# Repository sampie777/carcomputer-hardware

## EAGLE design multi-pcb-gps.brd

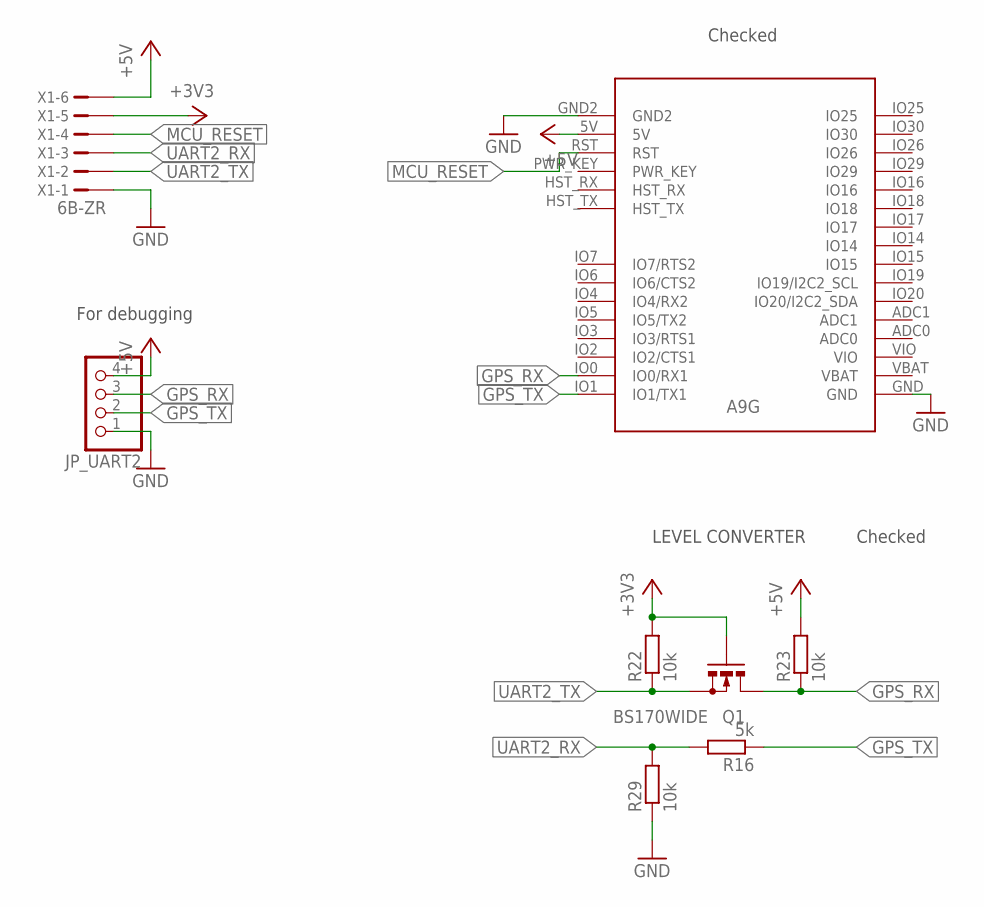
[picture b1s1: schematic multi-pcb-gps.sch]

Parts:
JP_UART2: PINHD-1X4; 1X04
Q1: BS170WIDE; SOT54E2
R16: 5k; 0207/7
R22, R23, R29: 10k; 0207/7
U$6: A9G
X1: 6B-ZR; B6B-ZR2.5

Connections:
+3V3: Q1.G, R22.2, X1.5
+5V: JP_UART2.4, R23.2, U$6.5V, X1.6
GND: JP_UART2.1, R29.1, U$6.GND, U$6.GND2, X1.1
GPS_RX: JP_UART2.3, Q1.D, R23.1, U$6.IO0 (IO0/RX1)
GPS_TX: JP_UART2.2, R16.1, U$6.IO1 (IO1/TX1)
MCU_RESET: U$6.RST, X1.4
UART2_RX: R16.2, R29.2, X1.3
UART2_TX: Q1.S, R22.1, X1.2

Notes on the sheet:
Checked
LEVEL CONVERTER
For debugging

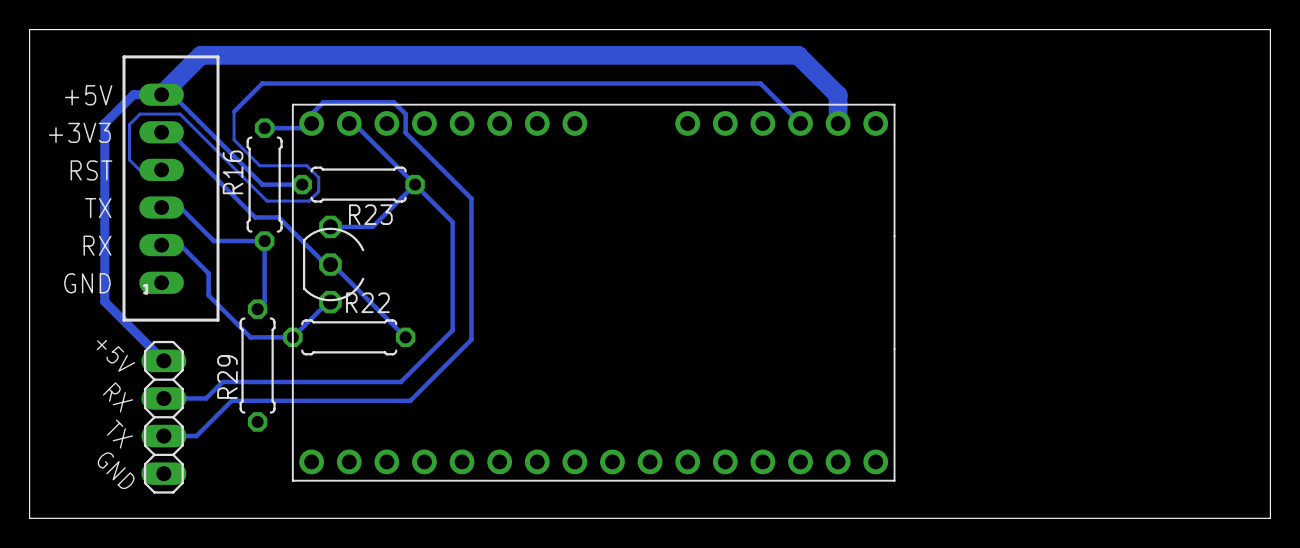
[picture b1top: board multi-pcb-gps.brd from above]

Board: 2 copper layers, 83.8 x 33.0 mm, 8 parts (0 on the bottom side), 8 nets.

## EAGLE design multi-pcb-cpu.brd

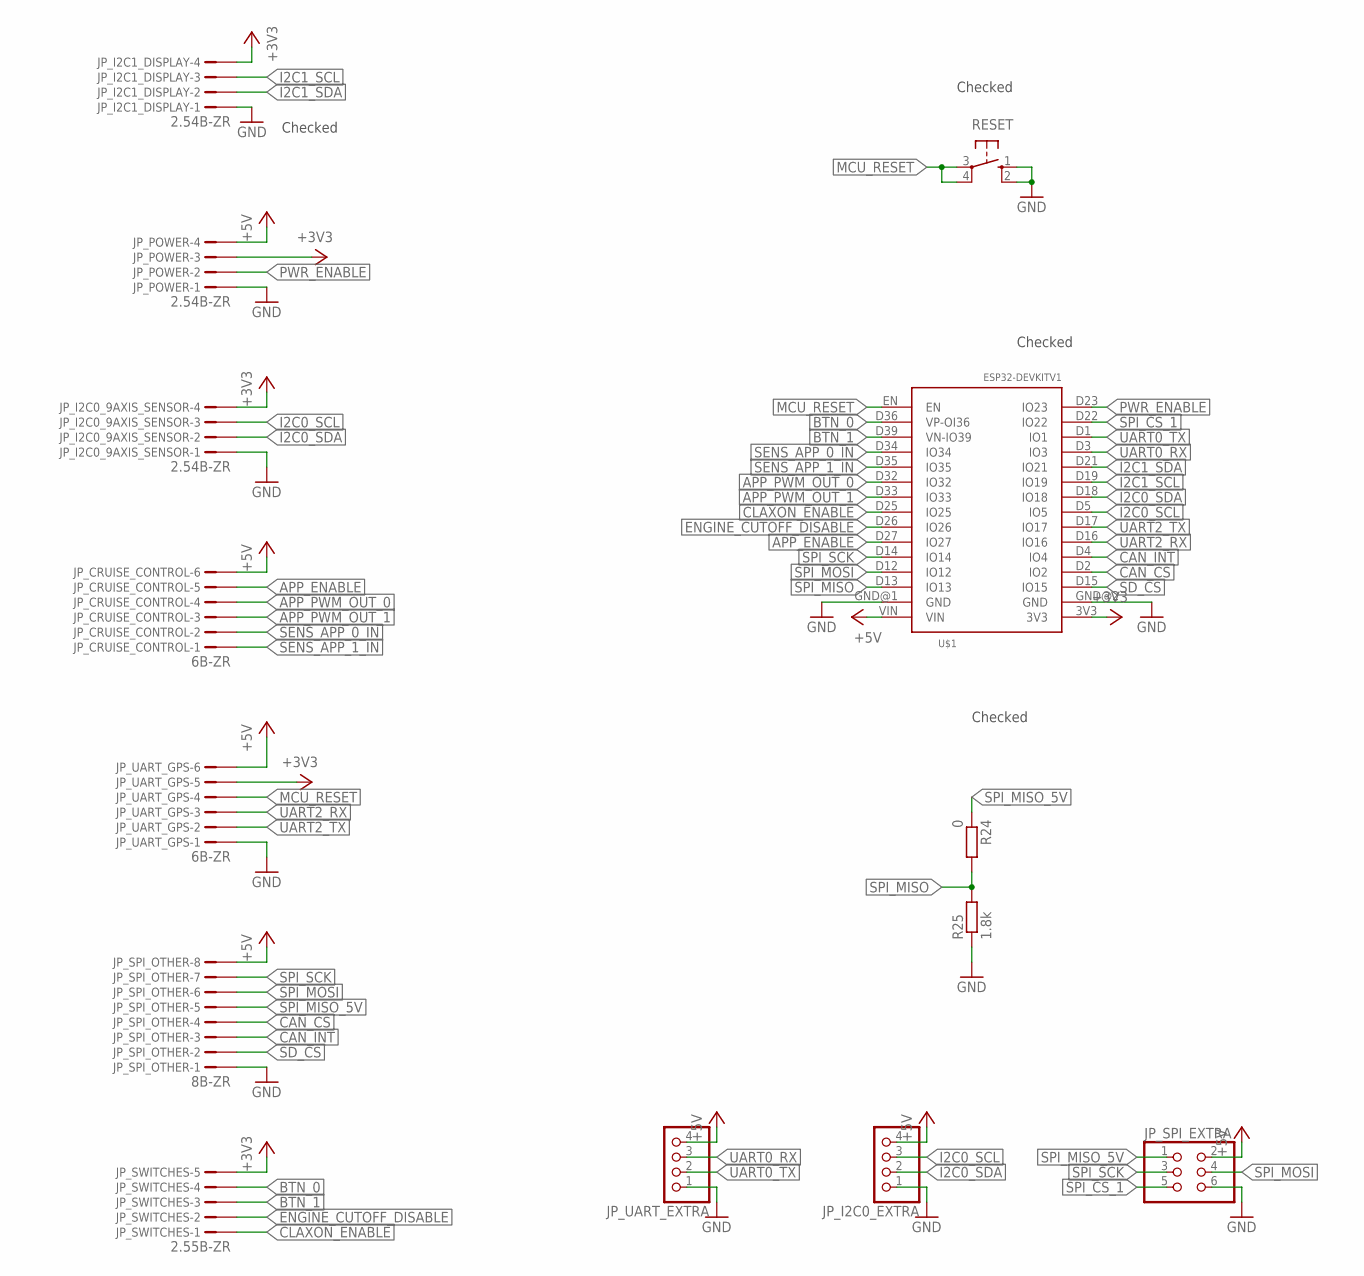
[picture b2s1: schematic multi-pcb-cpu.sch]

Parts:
JP_CRUISE_CONTROL: 6B-ZR; B6B-ZR2.5
JP_I2C0_9AXIS_SENSOR, JP_I2C1_DISPLAY: 2.54B-ZR; B4B-ZR2.5
JP_I2C0_EXTRA: PINHD-1X4; 1X04
JP_POWER: 2.54B-ZR; B4B-ZR2.5
JP_SPI_EXTRA: PINHD-2X3; 2X03
JP_SPI_OTHER: 8B-ZR; B8B-ZR2.5
JP_SWITCHES: 2.55B-ZR; B5B-ZR2.5
JP_UART_EXTRA: PINHD-1X4; 1X04
JP_UART_GPS: 6B-ZR; B6B-ZR2.5
R24: 0; 0207/7
R25: 1.8k; 0207/7
RESET: 10-XX; B3F-10XX
U$1: ESP32DEVKITV1; ESP32-DEVKITV1

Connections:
+3V3: JP_I2C0_9AXIS_SENSOR.4, JP_I2C1_DISPLAY.4, JP_POWER.3, JP_SWITCHES.5, JP_UART_GPS.5, U$1.3V3
+5V: JP_CRUISE_CONTROL.6, JP_I2C0_EXTRA.4, JP_POWER.4, JP_SPI_EXTRA.2, JP_SPI_OTHER.8, JP_UART_EXTRA.4, JP_UART_GPS.6, U$1.VIN
APP_ENABLE: JP_CRUISE_CONTROL.5, U$1.D27 (IO27)
APP_PWM_OUT_0: JP_CRUISE_CONTROL.4, U$1.D32 (IO32)
APP_PWM_OUT_1: JP_CRUISE_CONTROL.3, U$1.D33 (IO33)
BTN_0: JP_SWITCHES.4, U$1.D36 (VP-OI36)
BTN_1: JP_SWITCHES.3, U$1.D39 (VN-IO39)
CAN_CS: JP_SPI_OTHER.4, U$1.D2 (IO2)
CAN_INT: JP_SPI_OTHER.3, U$1.D4 (IO4)
CLAXON_ENABLE: JP_SWITCHES.1, U$1.D25 (IO25)
ENGINE_CUTOFF_DISABLE: JP_SWITCHES.2, U$1.D26 (IO26)
GND: JP_I2C0_9AXIS_SENSOR.1, JP_I2C0_EXTRA.1, JP_I2C1_DISPLAY.1, JP_POWER.1, JP_SPI_EXTRA.6, JP_SPI_OTHER.1, JP_UART_EXTRA.1, JP_UART_GPS.1, R25.1, RESET.1 (S), RESET.2 (S1), U$1.GND@1 (GND), U$1.GND@2 (GND)
I2C0_SCL: JP_I2C0_9AXIS_SENSOR.3, JP_I2C0_EXTRA.3, U$1.D5 (IO5)
I2C0_SDA: JP_I2C0_9AXIS_SENSOR.2, JP_I2C0_EXTRA.2, U$1.D18 (IO18)
I2C1_SCL: JP_I2C1_DISPLAY.3, U$1.D19 (IO19)
I2C1_SDA: JP_I2C1_DISPLAY.2, U$1.D21 (IO21)
MCU_RESET: JP_UART_GPS.4, RESET.3, RESET.4 (P1), U$1.EN
PWR_ENABLE: JP_POWER.2, U$1.D23 (IO23)
SD_CS: JP_SPI_OTHER.2, U$1.D15 (IO15)
SENS_APP_0_IN: JP_CRUISE_CONTROL.2, U$1.D34 (IO34)
SENS_APP_1_IN: JP_CRUISE_CONTROL.1, U$1.D35 (IO35)
SPI_CS_1: JP_SPI_EXTRA.5, U$1.D22 (IO22)
SPI_MISO: R24.2, R25.2, U$1.D13 (IO13)
SPI_MISO_5V: JP_SPI_EXTRA.1, JP_SPI_OTHER.5, R24.1
SPI_MOSI: JP_SPI_EXTRA.4, JP_SPI_OTHER.6, U$1.D12 (IO12)
SPI_SCK: JP_SPI_EXTRA.3, JP_SPI_OTHER.7, U$1.D14 (IO14)
UART0_RX: JP_UART_EXTRA.3, U$1.D3 (IO3)
UART0_TX: JP_UART_EXTRA.2, U$1.D1 (IO1)
UART2_RX: JP_UART_GPS.3, U$1.D16 (IO16)
UART2_TX: JP_UART_GPS.2, U$1.D17 (IO17)

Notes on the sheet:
Checked

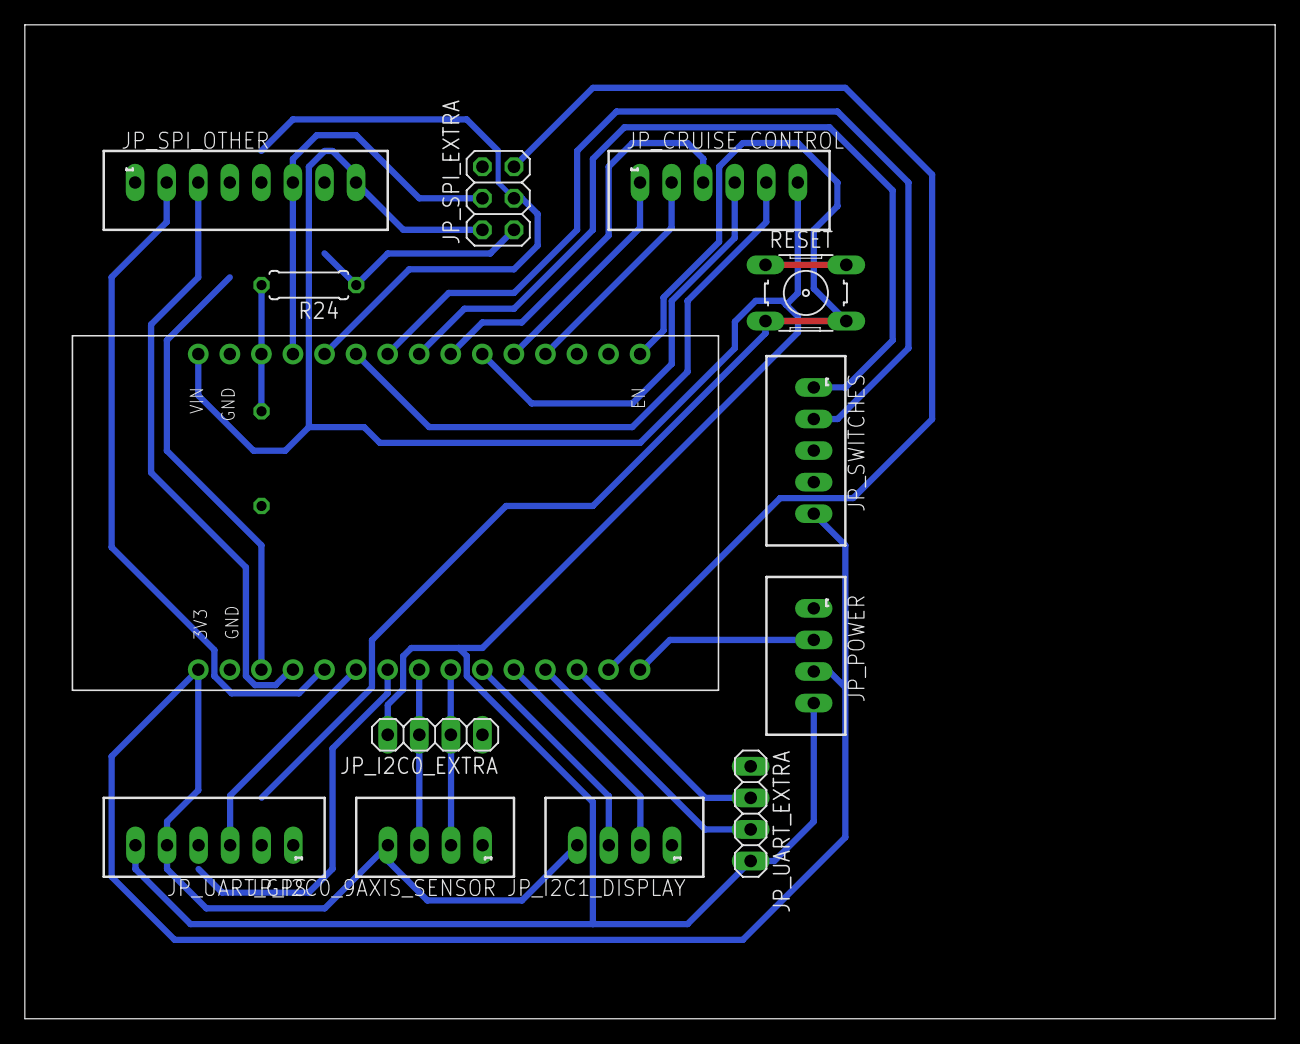
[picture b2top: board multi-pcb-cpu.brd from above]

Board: 2 copper layers, 100.6 x 80.0 mm, 14 parts (1 on the bottom side), 30 nets.

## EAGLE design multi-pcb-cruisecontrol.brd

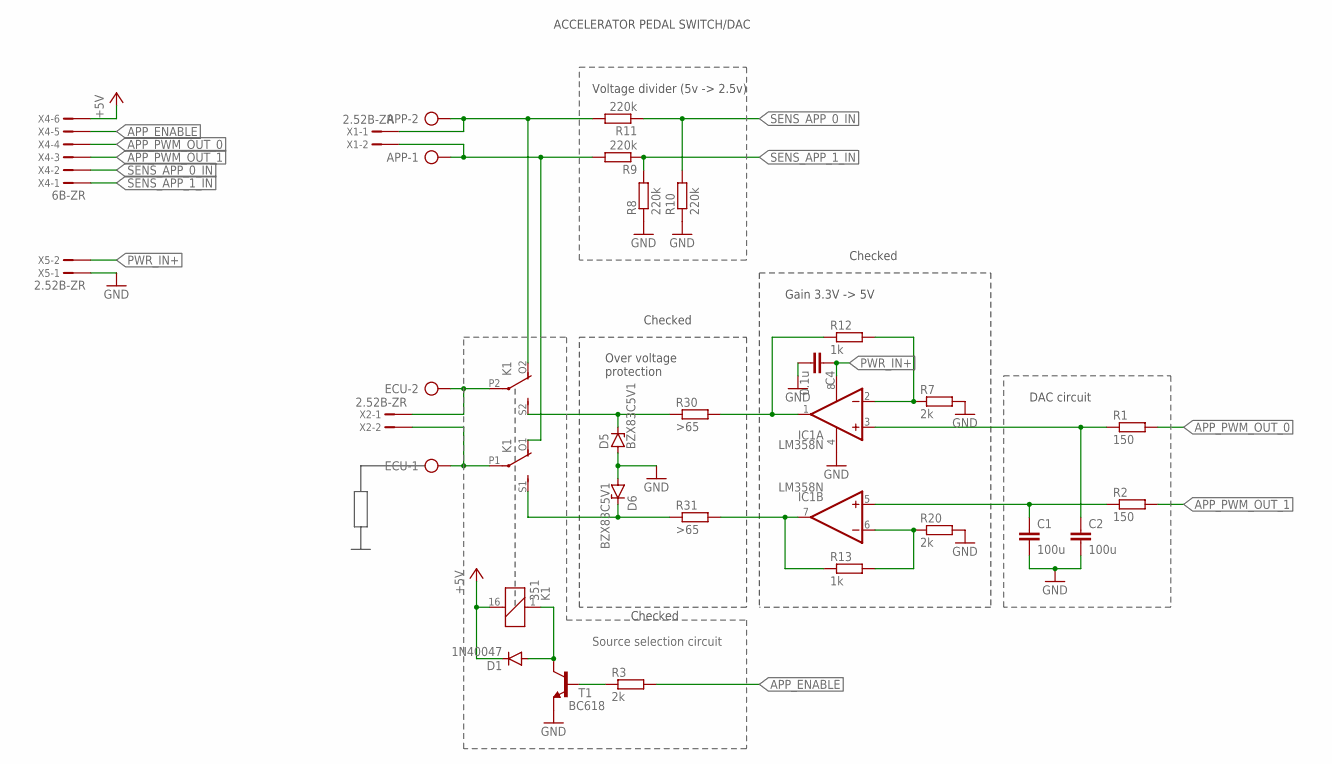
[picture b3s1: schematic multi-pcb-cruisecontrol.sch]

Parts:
APP: AK300/2
C1, C2: 100u; C025-050X050
C4: 0.1u; C025-050X050
D1: 1N40047; DO41-7.6
D5, D6: BZX83C5V1; DO41Z7.6
ECU: AK300/2
IC1: LM358N; DIL08
K1: 351
R1, R2: 150; 0207/7
R3, R7, R20: 2k; 0207/7
R8, R9, R10, R11: 220k; 0207/7
R12, R13: 1k; 0207/7
R30, R31: >65; 0207/7
T1: BC618; TO92-EBC
X1, X2, X5: 2.52B-ZR; B2B-ZR2.5
X4: 6B-ZR; B6B-ZR2.5

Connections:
+5V: D1.C, K1.16 (2), X4.6
APP_0_IN: APP.2, K1.O2 (O), R11.2, X1.1
APP_1_IN: APP.1, K1.O1 (O), R9.2, X1.2
APP_ENABLE: R3.2, X4.5
APP_PWM_OUT_0: R1.2, X4.4
APP_PWM_OUT_1: R2.2, X4.3
GND: C1.2, C2.2, C4.2, D5.A, D6.A, IC1.4 (V-), R7.2, R8.1, R10.1, R20.2, T1.E, X5.1
unnamed: D1.A, K1.1, T1.C
unnamed: R3.1, T1.B
unnamed: D6.C, K1.S1 (S), R31.1
unnamed: IC1.1 (OUT), R12.1, R30.2
unnamed: ECU.2, K1.P2, X2.1
unnamed: ECU.1, K1.P1, X2.2
unnamed: C2.1, IC1.3 (+IN), R1.1
unnamed: C1.1, IC1.5 (+IN), R2.1
unnamed: IC1.2 (-IN), R7.1, R12.2
unnamed: IC1.6 (-IN), R13.2, R20.1
unnamed: D5.C, K1.S2 (S), R30.1
unnamed: IC1.7 (OUT), R13.1, R31.2
PWR_IN+: C4.1, IC1.8 (V+), X5.2
SENS_APP_0_IN: R10.2, R11.1, X4.2
SENS_APP_1_IN: R8.2, R9.1, X4.1

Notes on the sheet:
Voltage divider (5v -> 2.5v)
DAC circuit
Source selection circuit
ACCELERATOR PEDAL SWITCH/DAC
Gain 3.3V -> 5V
Over voltage protection
Checked

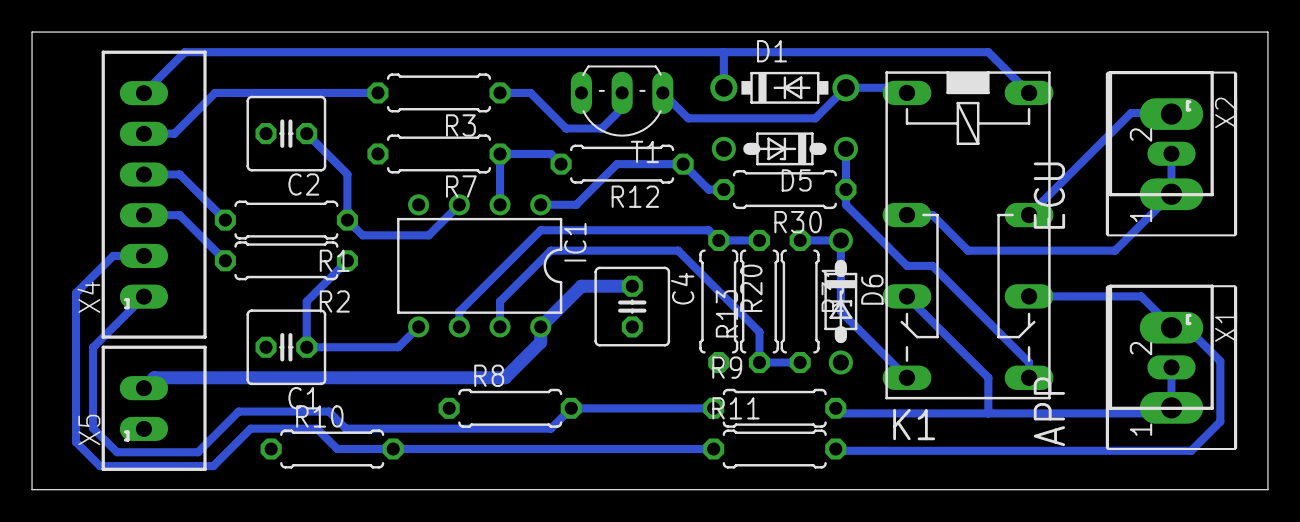
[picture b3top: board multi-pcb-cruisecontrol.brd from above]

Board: 2 copper layers, 77.1 x 28.6 mm, 28 parts (0 on the bottom side), 22 nets.

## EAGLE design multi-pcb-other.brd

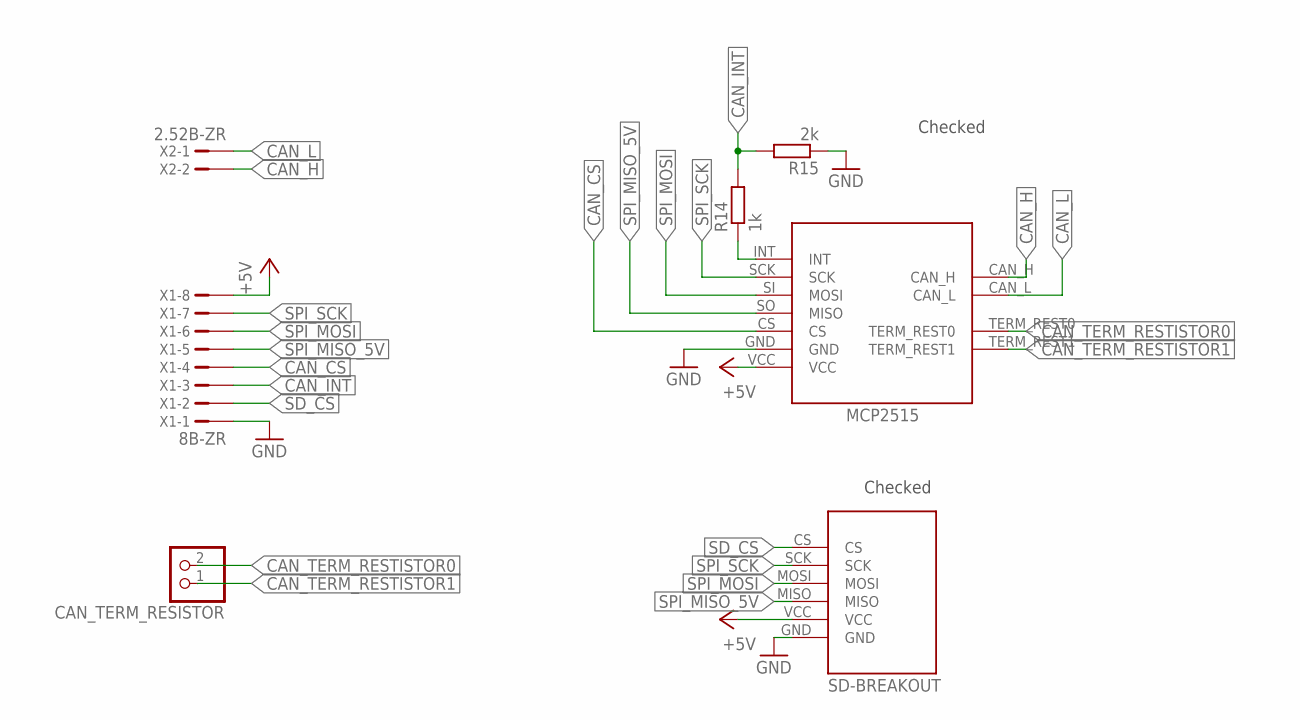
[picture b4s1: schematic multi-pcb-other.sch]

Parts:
CAN_TERM_RESISTOR: PINHD-1X2; 1X02
R14: 1k; 0207/10
R15: 2k; 0207/10
U$2: MCP2515_DEVBOARDMCP2515_DEVBOARD_INVERTED_NODRILL; MCP2515_DEVBOARD_INVERTED_NODRILL
U$5: HKD-MICRO-SD-BREAKOUT; HKD-MICRO-SD-BREAKOUT_NODRILL
X1: 8B-ZR; B8B-ZR2.5
X2: 2.52B-ZR; B2B-ZR2.5

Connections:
+5V: U$2.VCC, U$5.VCC, X1.8
CAN_CS: U$2.CS, X1.4
CAN_H: U$2.CAN_H, X2.2
CAN_INT: R14.2, R15.2, X1.3
CAN_L: U$2.CAN_L, X2.1
CAN_TERM_RESTISTOR0: CAN_TERM_RESISTOR.2, U$2.TERM_REST0
CAN_TERM_RESTISTOR1: CAN_TERM_RESISTOR.1, U$2.TERM_REST1
GND: R15.1, U$2.GND, U$5.GND, X1.1
unnamed: R14.1, U$2.INT
SD_CS: U$5.CS, X1.2
SPI_MISO_5V: U$2.SO (MISO), U$5.MISO, X1.5
SPI_MOSI: U$2.SI (MOSI), U$5.MOSI, X1.6
SPI_SCK: U$2.SCK, U$5.SCK, X1.7

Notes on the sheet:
Checked

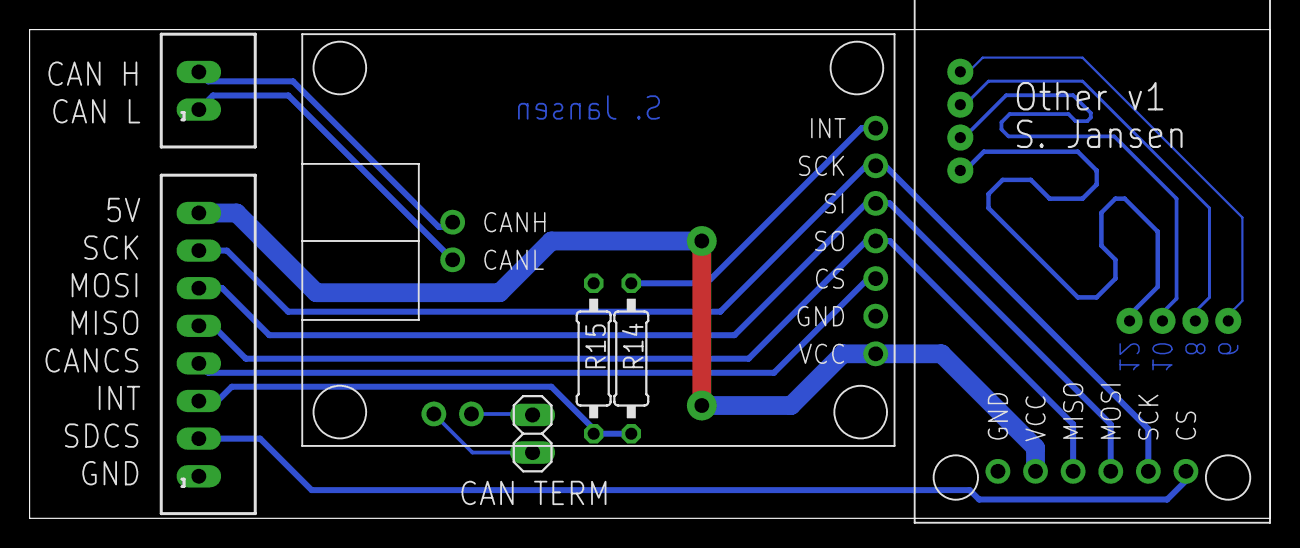
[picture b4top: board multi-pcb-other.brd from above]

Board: 2 copper layers, 83.8 x 33.0 mm, 7 parts (0 on the bottom side), 13 nets.

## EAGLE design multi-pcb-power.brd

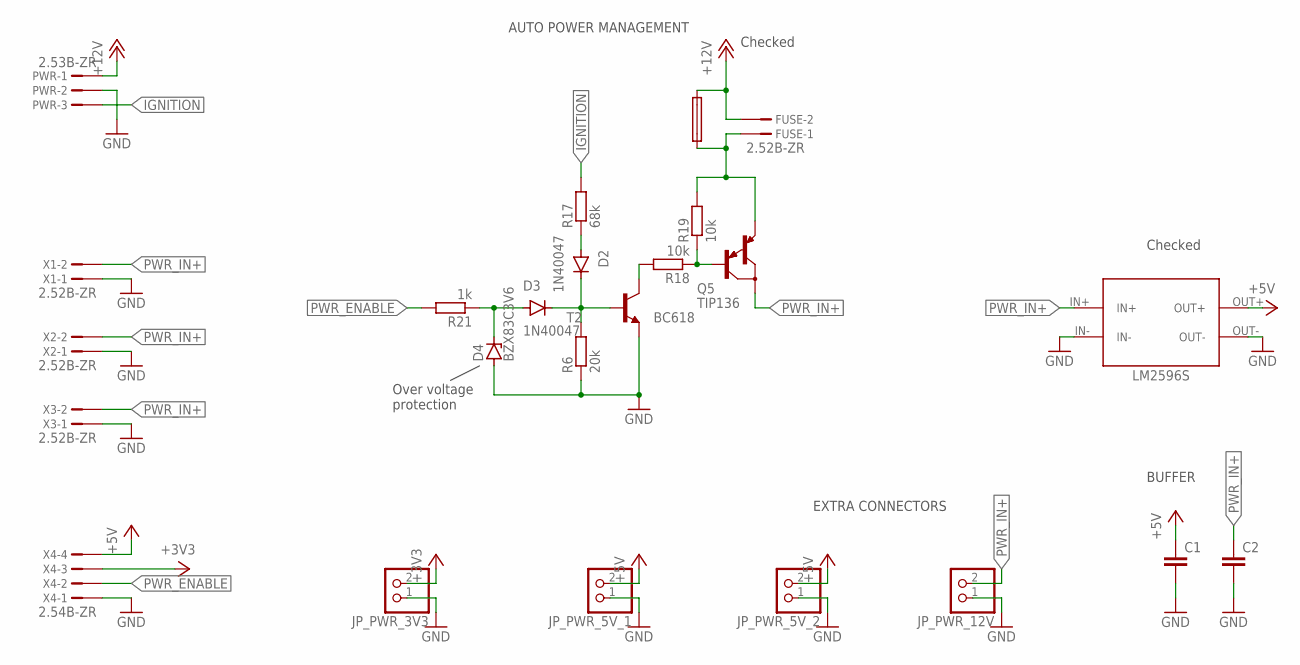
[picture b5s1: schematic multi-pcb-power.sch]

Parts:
C1, C2: C-EU050-075X075; C050-075X075
D2, D3: 1N40047; DO41-7.6
D4: BZX83C3V6; DO41Z7.6
FUSE: 2.52B-ZR; B2B-ZR2.5
JP_PWR_3V3, JP_PWR_5V_1, JP_PWR_5V_2, JP_PWR_12V: PINHD-1X2; 1X02
PWR: 2.53B-ZR; B3B-ZR2.5
Q5: TIP136; TO220
R6: 20k; 0207/7
R17: 68k; 0207/7
R18, R19: 10k; 0207/7
R21: 1k; 0207/7
T2: BC618; TO92-EBC
U$1: FUSE; FB-5X20
U$4: LM2596S
X1, X2, X3: 2.52B-ZR; B2B-ZR2.5
X4: 2.54B-ZR; B4B-ZR2.5

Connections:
+3V3: JP_PWR_3V3.2, X4.3
+5V: C1.1, JP_PWR_5V_1.2, JP_PWR_5V_2.2, U$4.OUT+, X4.4
+12V: FUSE.2, PWR.1, U$1.P$3, U$1.P$4
GND: C1.2, C2.2, D4.A, JP_PWR_3V3.1, JP_PWR_5V_1.1, JP_PWR_5V_2.1, JP_PWR_12V.1, PWR.2, R6.1, T2.E, U$4.IN-, U$4.OUT-, X1.1, X2.1, X3.1, X4.1
IGNITION: PWR.3, R17.2
unnamed: D2.C, D3.C, R6.2, T2.B
unnamed: D3.A, D4.C, R21.1
unnamed: D2.A, R17.1
unnamed: Q5.1 (B), R18.1, R19.1
unnamed: R18.2, T2.C
unnamed: FUSE.1, Q5.3 (E), R19.2, U$1.P$1, U$1.P$2
PWR_ENABLE: R21.2, X4.2
PWR_IN+: C2.1, JP_PWR_12V.2, Q5.2 (C), U$4.IN+, X1.2, X2.2, X3.2

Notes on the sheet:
Over voltage protection
AUTO POWER MANAGEMENT
EXTRA CONNECTORS
Checked
BUFFER

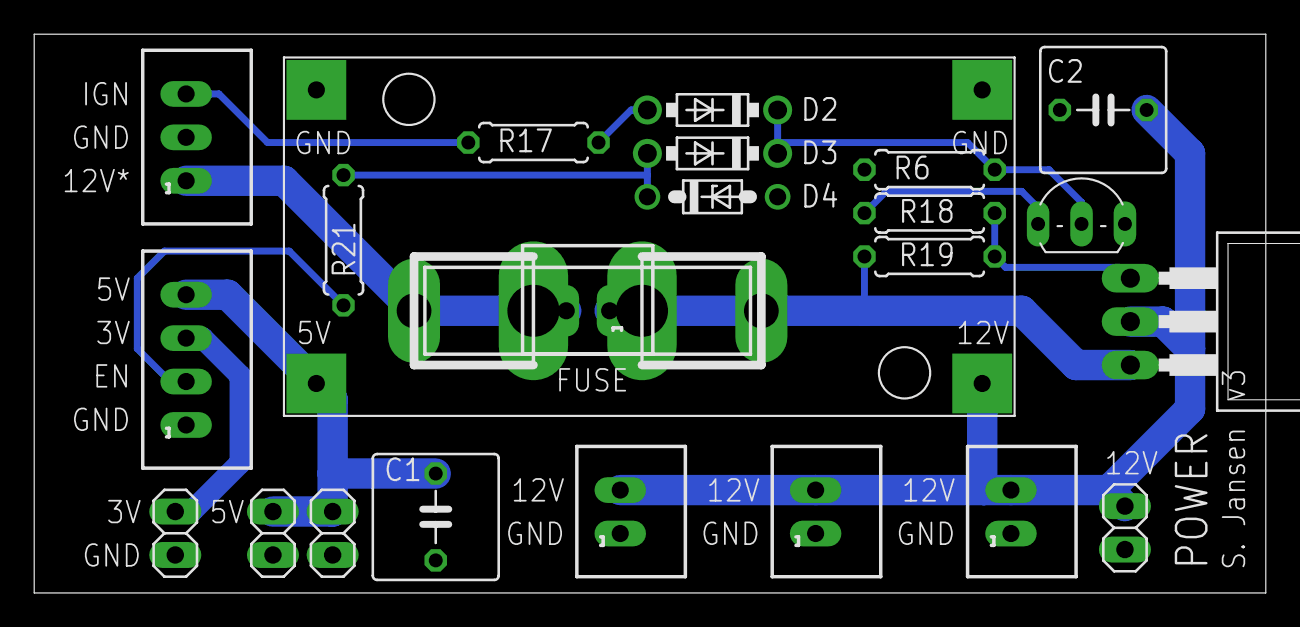
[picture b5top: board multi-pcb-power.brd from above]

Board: 2 copper layers, 72.1 x 32.7 mm, 24 parts (0 on the bottom side), 13 nets.

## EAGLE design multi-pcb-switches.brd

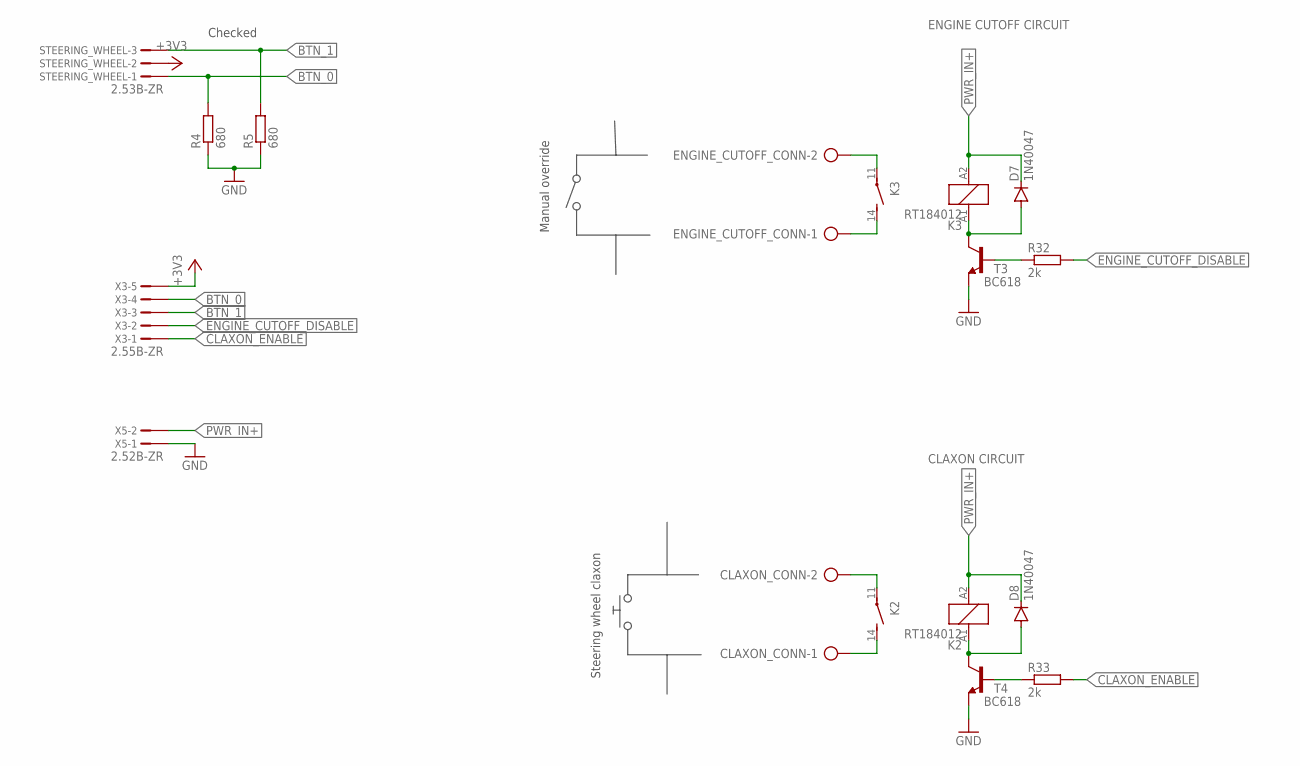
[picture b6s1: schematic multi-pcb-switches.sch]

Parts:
CLAXON_CONN: AK300/2
D7, D8: 1N40047; DO41-7.6
ENGINE_CUTOFF_CONN: AK300/2
K2, K3: RT184012; RT-N/O12A3.5
R4, R5: 680; 0207/7
R32, R33: 2k; 0207/7
STEERING_WHEEL: 2.53B-ZR; B3B-ZR2.5
T3, T4: BC618; TO92-EBC
X3: 2.55B-ZR; B5B-ZR2.5
X5: 2.52B-ZR; B2B-ZR2.5

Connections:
+3V3: STEERING_WHEEL.2, X3.5
BTN_0: R4.2, STEERING_WHEEL.1, X3.4
BTN_1: R5.2, STEERING_WHEEL.3, X3.3
CLAXON_ENABLE: R33.2, X3.1
ENGINE_CUTOFF_DISABLE: R32.2, X3.2
GND: R4.1, R5.1, T3.E, T4.E, X5.1
unnamed: ENGINE_CUTOFF_CONN.2, K3.11
unnamed: ENGINE_CUTOFF_CONN.1, K3.14 (S)
unnamed: D7.A, K3.A1 (1), T3.C
unnamed: D8.A, K2.A1 (1), T4.C
unnamed: R33.1, T4.B
unnamed: R32.1, T3.B
unnamed: CLAXON_CONN.2, K2.11
unnamed: CLAXON_CONN.1, K2.14 (S)
PWR_IN+: D7.C, D8.C, K2.A2 (2), K3.A2 (2), X5.2

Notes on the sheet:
Checked
ENGINE CUTOFF CIRCUIT
Manual override
CLAXON CIRCUIT
Steering wheel claxon

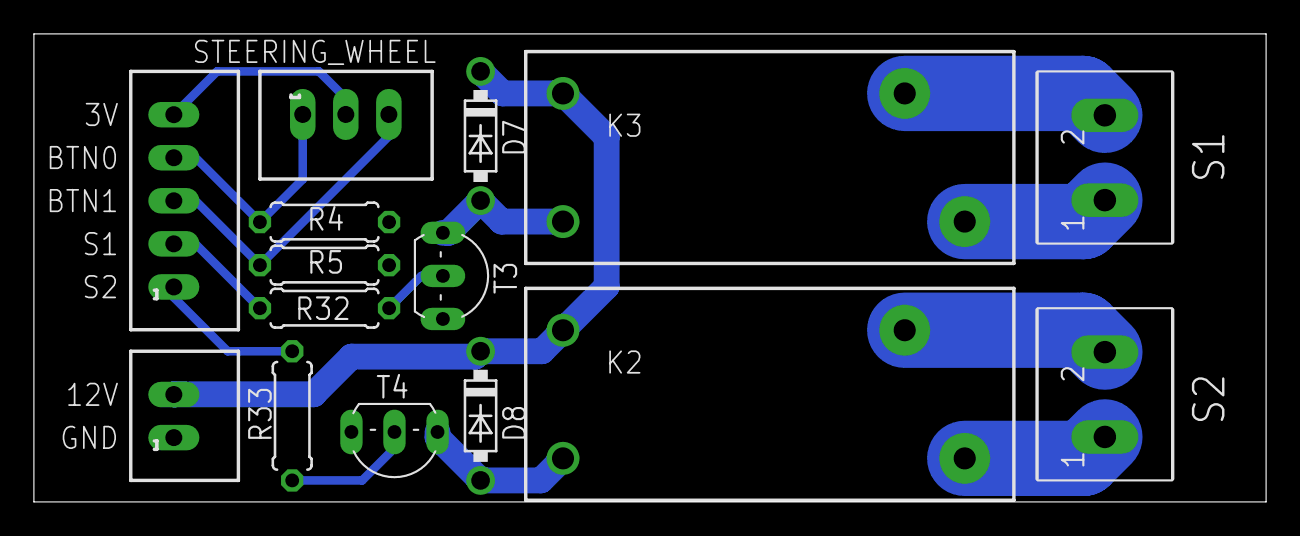
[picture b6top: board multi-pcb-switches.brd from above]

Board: 2 copper layers, 72.7 x 27.6 mm, 15 parts (0 on the bottom side), 15 nets.

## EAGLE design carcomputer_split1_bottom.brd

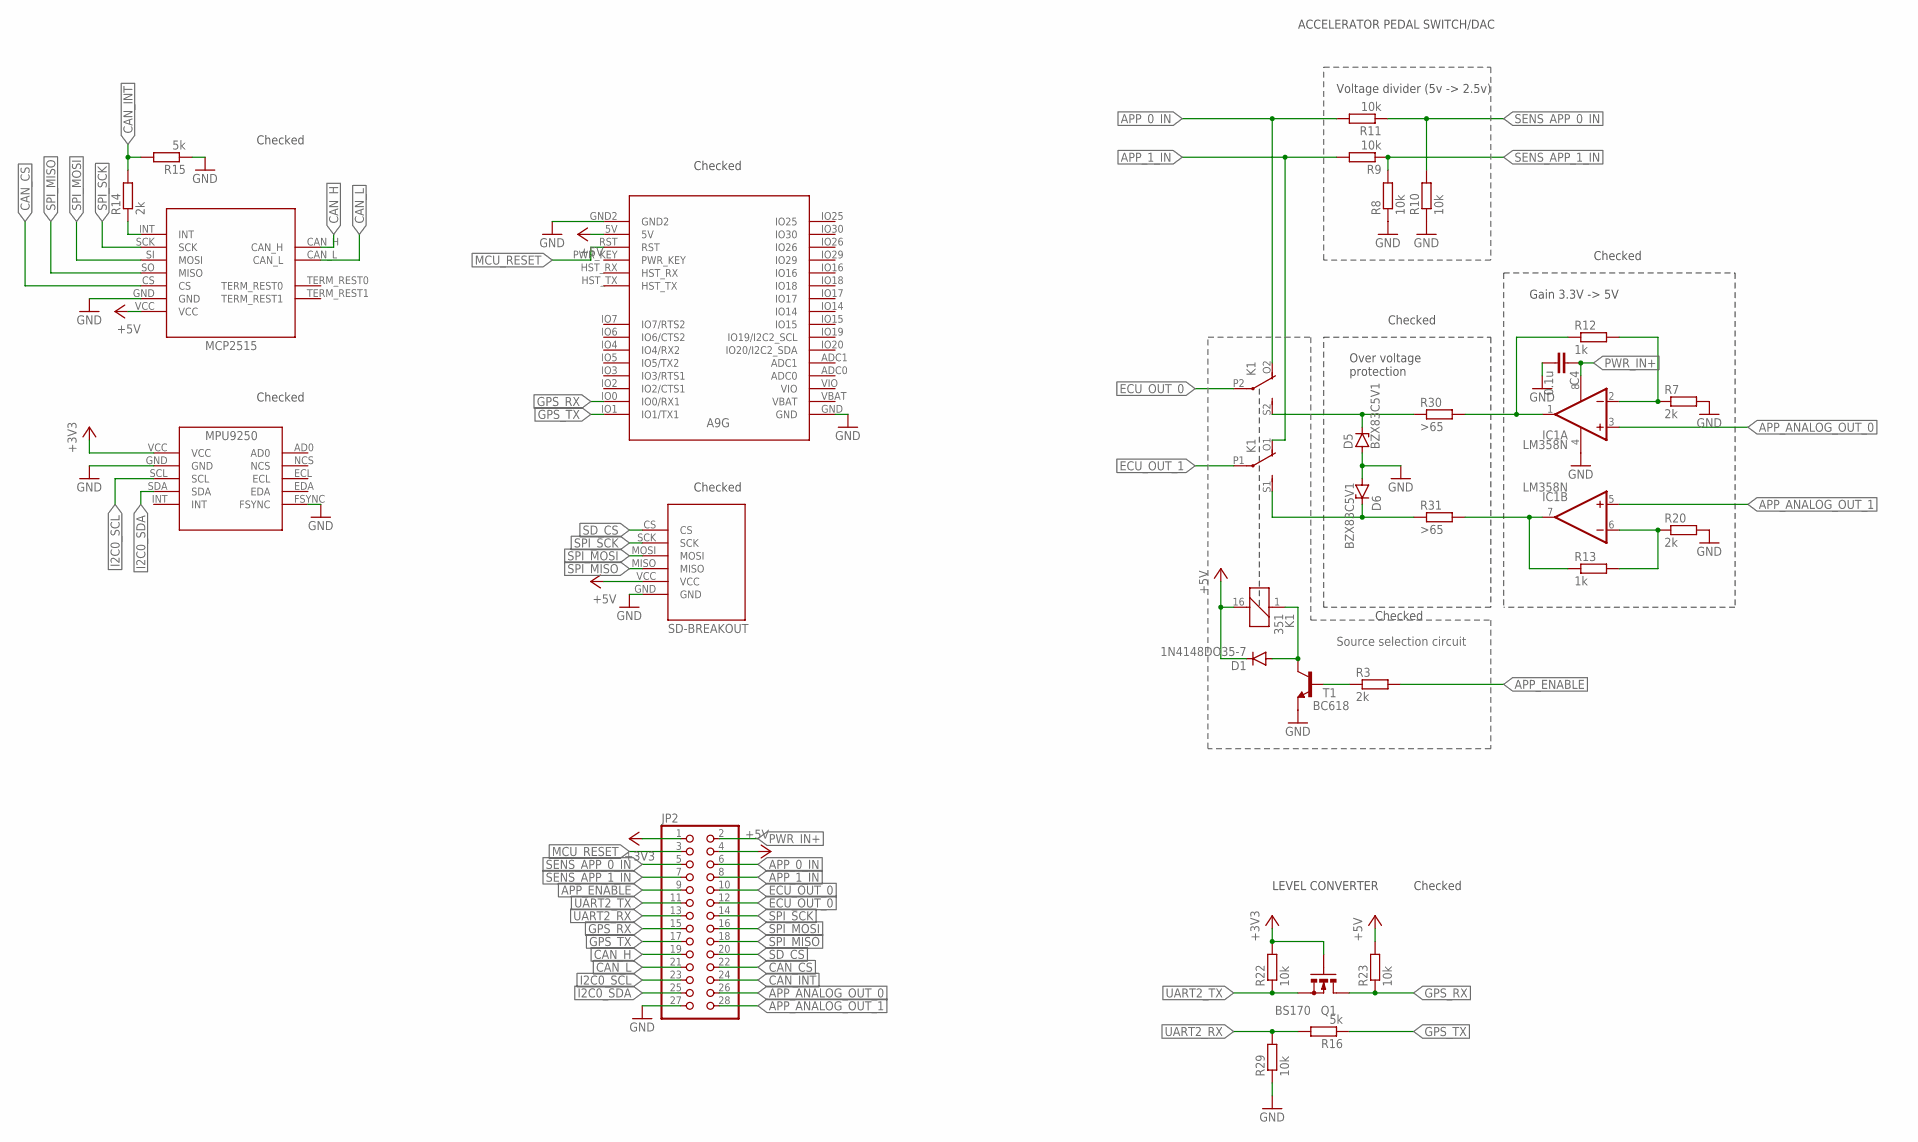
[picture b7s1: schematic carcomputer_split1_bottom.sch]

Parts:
C4: 0.1u; C025-050X050
D1: 1N4148DO35-7; DO35-7
D5, D6: BZX83C5V1; DO41Z10
IC1: LM358N; DIL08
JP2: PINHD-2X14; 2X14
K1: 351
Q1: BS170; SOT54E
R3, R7, R14, R20: 2k; 0207/7
R8, R9, R10, R11, R22, R23, R29: 10k; 0207/7
R12, R13: 1k; 0207/7
R15, R16: 5k; 0207/7
R30, R31: >65; 0207/7
T1: BC618; TO92-EBC
U$2: MCP2515_DEVBOARDINVERTED; MCP2515_DEVBOARD_INVERTED
U$3: MPU9250_BREAKOUT
U$5: HKD-MICRO-SD-BREAKOUT
U$6: A9G

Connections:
+3V3: JP2.1, Q1.G, R22.2, U$3.VCC
+5V: D1.C, JP2.4, K1.16 (2), R23.2, U$2.VCC, U$5.VCC, U$6.5V
APP_0_IN: JP2.6, K1.O2 (O), R11.2
APP_1_IN: JP2.8, K1.O1 (O), R9.2
APP_ANALOG_OUT_0: IC1.3 (+IN), JP2.26
APP_ANALOG_OUT_1: IC1.5 (+IN), JP2.28
APP_ENABLE: JP2.9, R3.2
CAN_CS: JP2.22, U$2.CS
CAN_H: JP2.19, U$2.CAN_H
CAN_INT: JP2.24, R14.2, R15.2
CAN_L: JP2.21, U$2.CAN_L
ECU_OUT_0: JP2.10, JP2.12, K1.P2
ECU_OUT_1: K1.P1
GND: C4.2, D5.A, D6.A, IC1.4 (V-), JP2.27, R7.2, R8.1, R10.1, R15.1, R20.2, R29.1, T1.E, U$2.GND, U$3.FSYNC, U$3.GND, U$5.GND, U$6.GND, U$6.GND2
GPS_RX: JP2.15, Q1.D, R23.1, U$6.IO0 (IO0/RX1)
GPS_TX: JP2.17, R16.1, U$6.IO1 (IO1/TX1)
I2C0_SCL: JP2.23, U$3.SCL
I2C0_SDA: JP2.25, U$3.SDA
MCU_RESET: JP2.3, U$6.RST
unnamed: D1.A, K1.1, T1.C
unnamed: R3.1, T1.B
unnamed: D6.C, K1.S1 (S), R31.1
unnamed: IC1.1 (OUT), R12.1, R30.2
unnamed: R14.1, U$2.INT
unnamed: IC1.2 (-IN), R7.1, R12.2
unnamed: IC1.6 (-IN), R13.2, R20.1
unnamed: D5.C, K1.S2 (S), R30.1
unnamed: IC1.7 (OUT), R13.1, R31.2
PWR_IN+: C4.1, IC1.8 (V+), JP2.2
SD_CS: JP2.20, U$5.CS
SENS_APP_0_IN: JP2.5, R10.2, R11.1
SENS_APP_1_IN: JP2.7, R8.2, R9.1
SPI_MISO: JP2.18, U$2.SO (MISO), U$5.MISO
SPI_MOSI: JP2.16, U$2.SI (MOSI), U$5.MOSI
SPI_SCK: JP2.14, U$2.SCK, U$5.SCK
UART2_RX: JP2.13, R16.2, R29.2
UART2_TX: JP2.11, Q1.S, R22.1

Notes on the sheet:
Voltage divider (5v -> 2.5v)
Source selection circuit
ACCELERATOR PEDAL SWITCH/DAC
Gain 3.3V -> 5V
Over voltage protection
Checked
LEVEL CONVERTER

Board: 2 copper layers, 30 parts (1 on the bottom side), 36 nets, no tracks yet.

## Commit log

2022-08-15 Git init
2022-08-15 Include custom libraries
2022-08-16 Added alternative power circuit. Added connection jumpers. Remapped some pins.
2022-08-16 Added SD card module (footprint is not accurate)
2022-08-17 Added voltage divider to input APP"
2022-08-24 Added A9G GPS unit. Removed backup files from git
2022-08-24 Changed GPS level converter to external resistor using level converter internal resistor
2022-08-24 Improved gitignore to ignore backup files
2022-08-25 Fixed power circuit
2022-09-02 Fixed 3V->5V gas pedal converter at high frequencies with opamp after DAC
2022-09-02 Fixed overvoltage protection on gas pedal circuit
2022-09-03 Fixed opamp power from battery power to controlled power supply
2022-09-03 Implemented circuits for claxon and engine cutoff
2022-09-07 unknown changes
2022-09-07 some various board layout options
2022-09-16 Routed almost first complete single board
2022-09-19 Added pinheaders connection for CAN terminator resistors
2022-09-19 Updated libraries
2022-09-19 Placed labels next to components. Rearranged silkscreen. Improved vias
2022-09-22 Updated silkscreen
2022-10-02 Improved traces. Renamed claxon/engine connections to more common names
2022-11-04 Added volage divider for MISO. Also added more space to some tracks.
2022-11-04 Fixed SD module length. Refitted SPI and I2C header.
2022-11-14 Added connector for fuse. Added extra safety boundries around high voltage areas.
2022-12-08 Renamed OBDII to CAN
2023-01-01 Repositioned labels to make them more clear. Also added pin labels to connectors.
2023-01-01 Added silkscreen markings for manually added wire connections
2023-01-25 refactor: Cleaned up old files
2023-01-25 Revert "refactor: Cleaned up old files"
    This reverts commit d2bb07198adf23b3f0d7dfa647e5ad3b2931060b.
    Reverting deletion of all files (including schematic which mustn't be deleted)
2023-01-25 refactor: Renamed files to match purpose of the file
2023-01-25 wip: Started with multi-pcb design
2023-01-29 Added board design rules
2023-01-29 small change
2023-02-14 Updated libraries with actual library files in use
2023-02-15 Routed more multi-pcb boards
2023-02-17 Reduced board spacing
2023-02-17 Fixed unalignment of connector
2023-02-17 some minor allignment improvement of fuse and power connector
2023-02-17 Made schematic more compact/clean
2024-09-16 Updated multi-switches board
2024-09-16 Added CPU board designs
2024-09-17 Updated layout of power circuit board
2024-09-19 Fixed PSU and fuse footprints. Also updated layout and added buffer capacitors.
2024-09-20 Final design for power circuit
2024-09-20 Updated gitignore
2024-09-21 Saved current board as v2
2024-09-21 Fixed mosfet direction for power in v3
2024-09-21 Updated trace width and ground plane for others
2024-09-25 PCB layout for multi-pcb-other
2024-12-26 updated some PCB's
2024-12-27 Last iteration of the board
